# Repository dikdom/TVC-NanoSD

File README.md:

# TVC-NanoSD
A microSD card handler IO card for the Videoton TV Computer.
Egy microSD kártya kezelő IO kártya a Videoton TV Computer számára.

## License
BSD 3-Clause License

## Description
This is a simple and cheap microSD handler card for the Hunarian 8 bit TVC computer. It emulates the cassette interface so it can load
and save .CAS files, it can read and write data files.

## Leírás
Ez egy egyszerű és viszonylag olcsón összerakható microSD kártya kezelő IO modul a magyar 8bites TVC számítógép felső bővítőjébe. A magnó 
interface-t emulálja, így .CAS file-okat olvas és ír (LOAD és SAVE parancs működik) illetve sima adat file-okat is létre lehet hozni vele
az SD kártyán.

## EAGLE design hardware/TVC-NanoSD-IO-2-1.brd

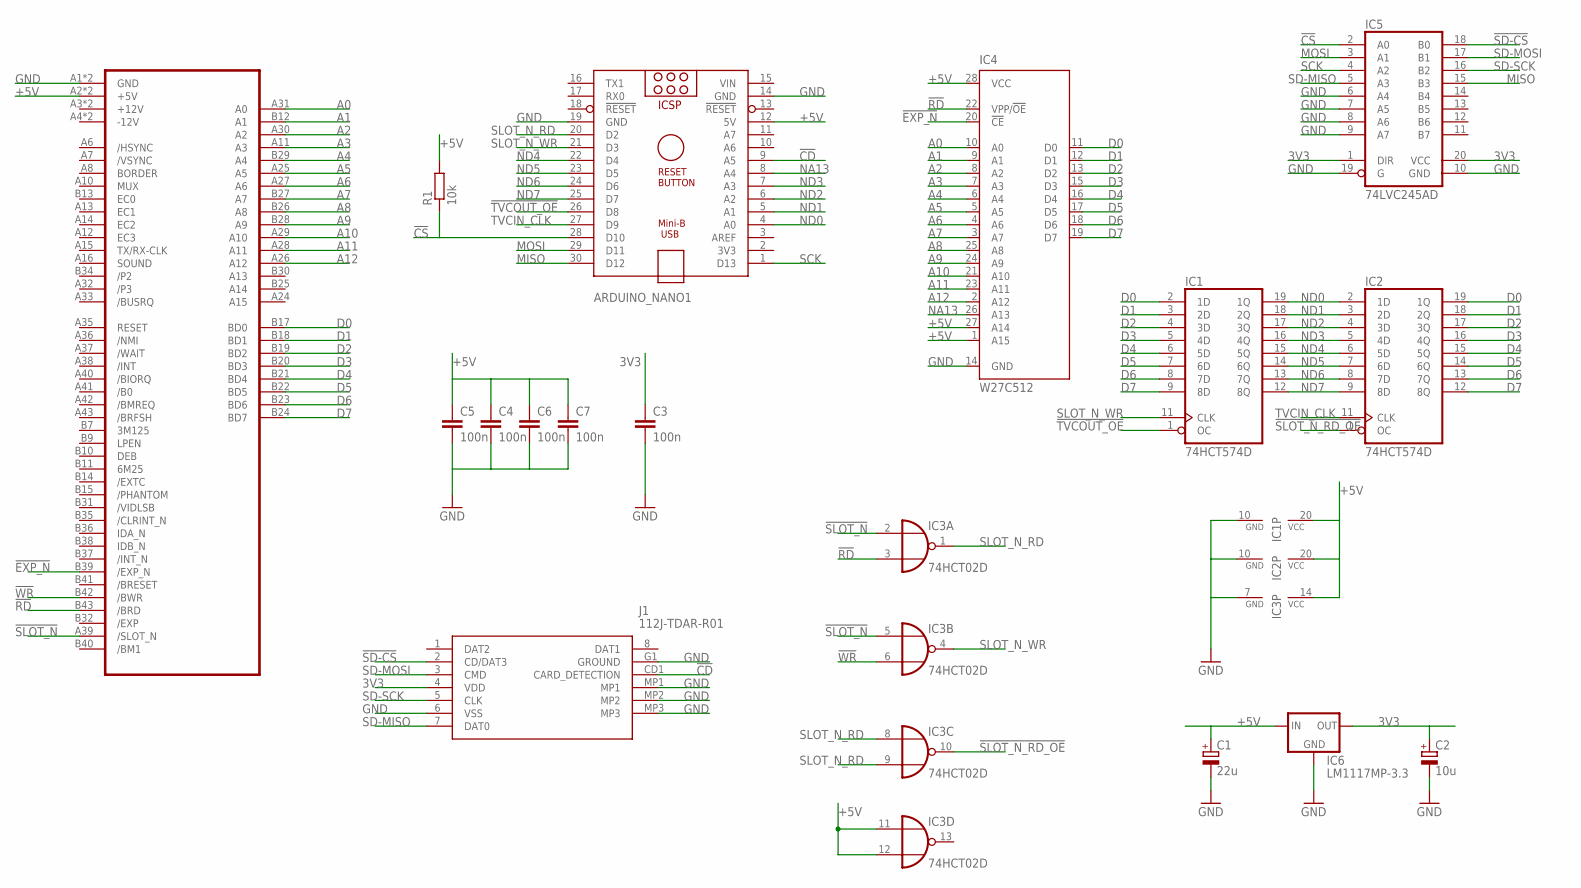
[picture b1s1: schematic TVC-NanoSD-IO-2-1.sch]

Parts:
ARDUINO_NANO1: ARDUINO_NANO
C1: 22u; PANASONIC_D
C2: 10u; PANASONIC_B
C3, C4, C5, C6, C7: 100n; C1206
CON1: TVC-EXP-HBA-COMMON; TVC-EXP-EDGE
IC1, IC2: 74HCT574D; SO20W
IC3: 74HCT02D; SO14
IC4: W27C512; DIL28-6
IC5: 74LVC245AD; SO20W
IC6: LM1117MP-3.3; SOT223
J1: 112J-TDAR-R01; 112JTDARR01
R1: 10k; R1206

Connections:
3V3: C2.+, C3.1, IC5.1 (DIR), IC5.20 (VCC), IC6.2 (OUT), IC6.4 (OUT), J1.4 (VDD)
!CD: ARDUINO_NANO1.9 (A5), J1.CD1 (CARD_DETECTION)
!CS: ARDUINO_NANO1.28 (D10), IC5.2 (A0), R1.1
!EXP_N: CON1.B39 (/EXP_N), IC4.20 (!CE)
!RD: CON1.B43 (/BRD), IC3.3 (I1), IC4.22 (VPP/!OE)
!SD-CS: IC5.18 (B0), J1.2 (CD/DAT3)
!SLOT_N: CON1.A39 (/SLOT_N), IC3.2 (I0), IC3.5 (I0)
!SLOT_N_RD_OE: IC2.1 (OC), IC3.10 (O)
!TVCOUT_OE: ARDUINO_NANO1.26 (D8), IC1.1 (OC)
!WR: CON1.B42 (/BWR), IC3.6 (I1)
+5V: ARDUINO_NANO1.12 (5V), C1.+, C4.1, C5.1, C6.1, C7.1, CON1.A2 (+5V), CON1.B2 (+5V), IC1.20 (VCC), IC2.20 (VCC), IC3.11 (I0), IC3.12 (I1), IC3.14 (VCC), IC4.1 (A15), IC4.27 (A14), IC4.28 (VCC), IC6.3 (IN), R1.2
A0: CON1.A31 (A0), IC4.10 (A0)
A1: CON1.B12 (A1), IC4.9 (A1)
A2: CON1.A30 (A2), IC4.8 (A2)
A3: CON1.A11 (A3), IC4.7 (A3)
A4: CON1.B29 (A4), IC4.6 (A4)
A5: CON1.A25 (A5), IC4.5 (A5)
A6: CON1.A27 (A6), IC4.4 (A6)
A7: CON1.B27 (A7), IC4.3 (A7)
A8: CON1.B26 (A8), IC4.25 (A8)
A9: CON1.B28 (A9), IC4.24 (A9)
A10: CON1.A29 (A10), IC4.21 (A10)
A11: CON1.A28 (A11), IC4.23 (A11)
A12: CON1.A26 (A12), IC4.2 (A12)
D0: CON1.B17 (BD0), IC1.2 (1D), IC2.19 (1Q), IC4.11 (D0)
D1: CON1.B18 (BD1), IC1.3 (2D), IC2.18 (2Q), IC4.12 (D1)
D2: CON1.B19 (BD2), IC1.4 (3D), IC2.17 (3Q), IC4.13 (D2)
D3: CON1.B20 (BD3), IC1.5 (4D), IC2.16 (4Q), IC4.15 (D3)
D4: CON1.B21 (BD4), IC1.6 (5D), IC2.15 (5Q), IC4.16 (D4)
D5: CON1.B22 (BD5), IC1.7 (6D), IC2.14 (6Q), IC4.17 (D5)
D6: CON1.B23 (BD6), IC1.8 (7D), IC2.13 (7Q), IC4.18 (D6)
D7: CON1.B24 (BD7), IC1.9 (8D), IC2.12 (8Q), IC4.19 (D7)
GND: ARDUINO_NANO1.14 (GND), ARDUINO_NANO1.19 (GND), C1.-, C2.-, C3.2, C4.2, C5.2, C6.2, C7.2, CON1.A1 (GND), CON1.B1 (GND), IC1.10 (GND), IC2.10 (GND), IC3.7 (GND), IC4.14 (GND), IC5.6 (A4), IC5.7 (A5), IC5.8 (A6), IC5.9 (A7), IC5.10 (GND), IC5.19 (G), IC6.1 (GND), J1.6 (VSS), J1.G1 (GROUND), J1.MP1, J1.MP2, J1.MP3
MISO: ARDUINO_NANO1.30 (D12), IC5.15 (B3)
MOSI: ARDUINO_NANO1.29 (D11), IC5.3 (A1)
NA13: ARDUINO_NANO1.8 (A4), IC4.26 (A13)
ND0: ARDUINO_NANO1.4 (A0), IC1.19 (1Q), IC2.2 (1D)
ND1: ARDUINO_NANO1.5 (A1), IC1.18 (2Q), IC2.3 (2D)
ND2: ARDUINO_NANO1.6 (A2), IC1.17 (3Q), IC2.4 (3D)
ND3: ARDUINO_NANO1.7 (A3), IC1.16 (4Q), IC2.5 (4D)
ND4: ARDUINO_NANO1.22 (D4), IC1.15 (5Q), IC2.6 (5D)
ND5: ARDUINO_NANO1.23 (D5), IC1.14 (6Q), IC2.7 (6D)
ND6: ARDUINO_NANO1.24 (D6), IC1.13 (7Q), IC2.8 (7D)
ND7: ARDUINO_NANO1.25 (D7), IC1.12 (8Q), IC2.9 (8D)
SCK: ARDUINO_NANO1.1 (D13), IC5.4 (A2)
SD-MISO: IC5.5 (A3), J1.7 (DAT0)
SD-MOSI: IC5.17 (B1), J1.3 (CMD)
SD-SCK: IC5.16 (B2), J1.5 (CLK)
SLOT_N_RD: ARDUINO_NANO1.20 (D2), IC3.1 (O), IC3.8 (I0), IC3.9 (I1)
SLOT_N_WR: ARDUINO_NANO1.21 (D3), IC1.11 (CLK), IC3.4 (O)
TVCIN_CLK: ARDUINO_NANO1.27 (D9), IC2.11 (CLK)
VIN: ARDUINO_NANO1.15 (VIN)

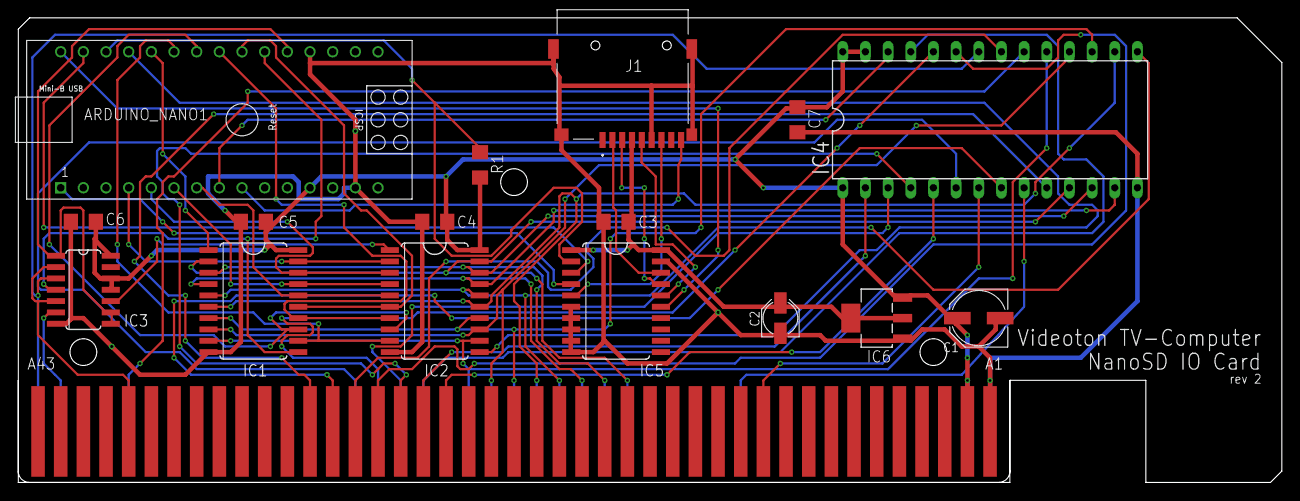
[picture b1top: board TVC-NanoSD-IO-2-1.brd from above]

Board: 2 copper layers, 141.6 x 52.0 mm, 17 parts (0 on the bottom side), 51 nets.

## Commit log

2021-08-09 Initial upload
    First commit without schematics and board source files
2021-08-09 Update README.md
    Initial description
2021-08-09 License update
2026-01-04 HW source files added
